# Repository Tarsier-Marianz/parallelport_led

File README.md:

# parallelport_led

A simple prototype board of **Parallel Port** (`LPT port`) controller.

A sample software source code that I used to control LEDs state of **Parallel Port** Controller can be found [here](https://github.com/Tarsier-Marianz/ParallelPort.LED.Controller), together with the executable file which is located inside [bin/Debug](https://github.com/Tarsier-Marianz/ParallelPort.LED.Controller/tree/master/ParallelPort.LED.Controller/bin/x86/Debug) folder.

`Feel free to use my software at your own risk. :D`

## Screenshots

# Credits
[KiCAD IDE](http://kicad-pcb.org/) letting me use a free software in designing PCB.

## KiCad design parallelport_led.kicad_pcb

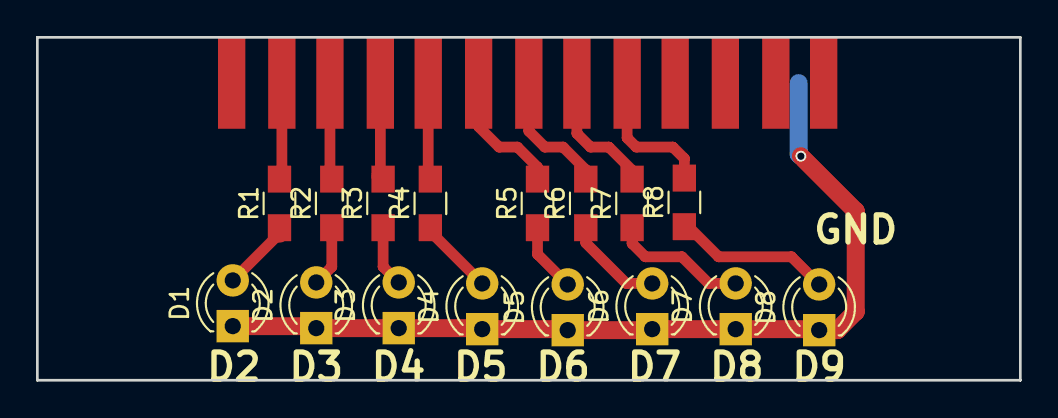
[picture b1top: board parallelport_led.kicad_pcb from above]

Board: 2 copper layers, 54.6 x 19.0 mm, 17 parts (0 on the bottom side), 17 nets.

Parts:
D1, D2, D3, D4, D5, D6, D7, D8: LED; LED_D3.0mm
J1: DB25; DB25F_CI
R1, R2, R3, R4, R5, R6, R7, R8: R; R_0805_HandSoldering

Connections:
/D0: J1.2, R1.2
/D1: J1.3, R2.2
/D2: J1.4, R3.2
/D3: J1.5, R4.2
/D4: J1.6, R5.2
/D5: J1.7, R6.2
/D6: J1.8, R7.2
/D7: J1.9, R8.2
/GND: D1.1, D2.1, D3.1, D4.1, D5.1, D6.1, D7.1, D8.1, J1.25
unnamed: D1.2, R1.1
unnamed: D2.2, R2.1
unnamed: D3.2, R3.1
unnamed: D4.2, R4.1
unnamed: D5.2, R5.1
unnamed: D6.2, R6.1
unnamed: D7.2, R7.1
unnamed: D8.2, R8.1

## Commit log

2018-03-21 >moved file references
2018-03-21 +readme repo overview
